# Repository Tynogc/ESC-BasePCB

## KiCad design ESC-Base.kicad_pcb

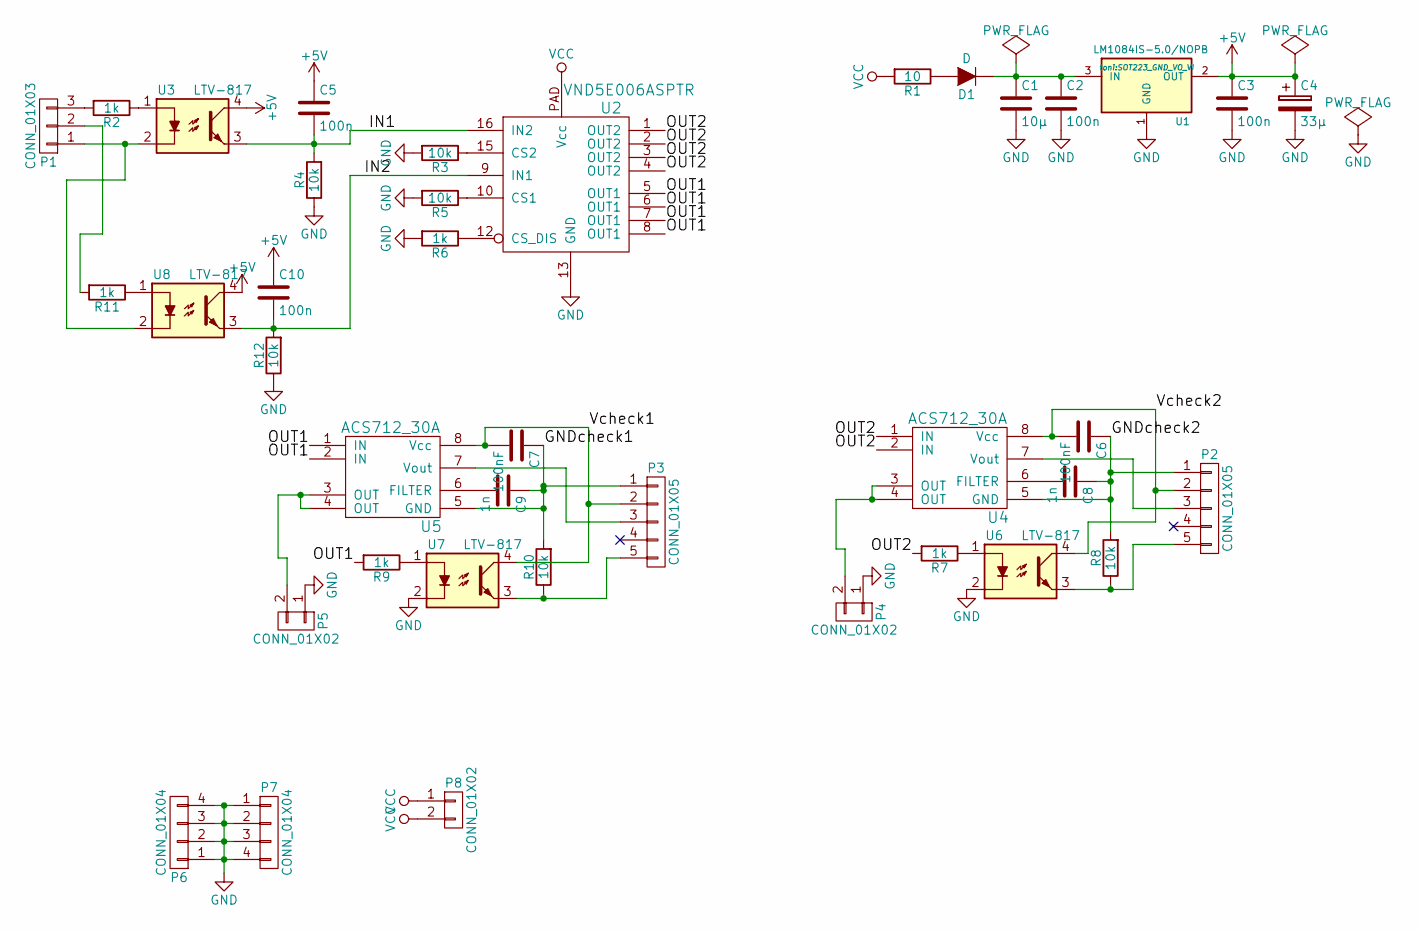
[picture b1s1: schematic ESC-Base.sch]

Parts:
C1: 10µ; C_0805_HandSoldering
C2, C3, C5, C10: 100n; C_0805_HandSoldering
C4: 33µ; c_elec_5x5.8
C6, C7: 100nF; C_0805_HandSoldering
C8, C9: 1n; C_0805_HandSoldering
D1: D; SOD-123
P1: CONN_01X03; Socket_Strip_Straight_1x03
P2, P3: CONN_01X05; Socket_Strip_Straight_1x05
P4, P5: CONN_01X02; PowerPole_1x2
P6, P7: CONN_01X04; Pin_Header_BIG_1x04
P8: CONN_01X02; Socket_Strip_Straight_1x02
R1: 10; R_0603_HandSoldering
R2, R6, R7, R9, R11: 1k; R_0603_HandSoldering
R3, R4, R5, R8, R10, R12: 10k; R_0603_HandSoldering
U1: LM1084IS-5.0/NOPB; SOT223_GND_VO_VI
U2: VND5E006ASPTR; POWER_SO16
U3, U6, U7, U8: LTV-817; SO-4
U4, U5: ACS712_30A; SOIC-8-N

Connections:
+5V: C3.1, C4.1, C5.1, C10.1, U1.2 (OUT), U3.4, U8.4
/GNDcheck1: C7.1, C9.1, P3.1, R10.2, U5.5 (GND)
/GNDcheck2: C6.1, C8.1, P2.1, R8.2, U4.5 (GND)
/IN1: C5.2, R4.2, U2.16 (IN2), U3.3
/IN2: C10.2, R12.2, U2.9 (IN1), U8.3
/OUT1: R9.2, U2.5 (OUT1), U2.6 (OUT1), U2.7 (OUT1), U2.8 (OUT1), U5.1 (IN), U5.2 (IN)
/OUT2: R7.2, U2.1 (OUT2), U2.2 (OUT2), U2.3 (OUT2), U2.4 (OUT2), U4.1 (IN), U4.2 (IN)
/Vcheck1: C7.2, P3.2, U5.8 (Vcc), U7.4
/Vcheck2: C6.2, P2.2, U4.8 (Vcc), U6.4
GND: C1.2, C2.2, C3.2, C4.2, P4.1, P5.1, P6.1, P6.2, P6.3, P6.4, P7.1, P7.2, P7.3, P7.4, R3.2, R4.1, R5.2, R6.2, R12.1, U1.1 (GND), U2.13 (GND), U6.2, U7.2
unnamed: C1.1, C2.1, D1.1 (K), U1.3 (IN)
unnamed: C8.2, U4.6 (FILTER)
unnamed: C9.2, U5.6 (FILTER)
unnamed: D1.2 (A), R1.1
unnamed: P1.1, U3.2, U8.2
unnamed: P1.2, R11.2
unnamed: P1.3, R2.2
unnamed: P2.3, U4.7 (Vout)
unnamed: P2.5, R8.1, U6.3
unnamed: P3.3, U5.7 (Vout)
unnamed: P3.5, R10.1, U7.3
unnamed: P4.2, U4.3 (OUT), U4.4 (OUT)
unnamed: P5.2, U5.3 (OUT), U5.4 (OUT)
unnamed: R2.1, U3.1
unnamed: R3.1, U2.15 (CS2)
unnamed: R5.1, U2.10 (CS1)
unnamed: R6.1, U2.12 (CS_DIS)
unnamed: R7.1, U6.1
unnamed: R9.1, U7.1
unnamed: R11.1, U8.1
VCC: P8.1, P8.2, R1.2, U2.PAD (Vcc)

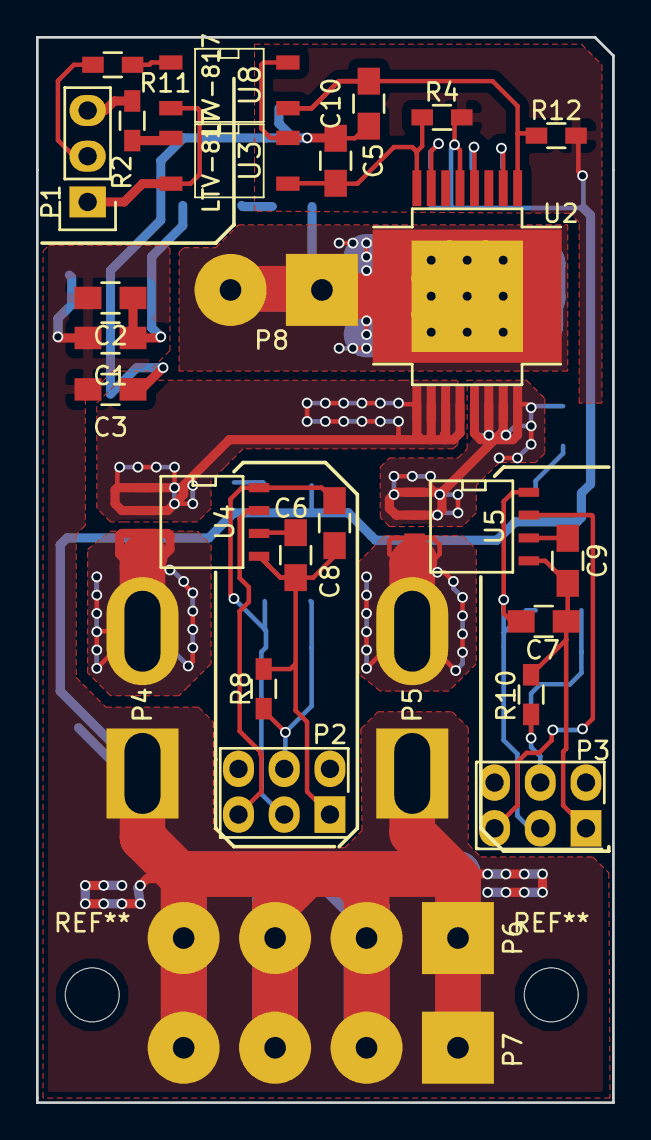
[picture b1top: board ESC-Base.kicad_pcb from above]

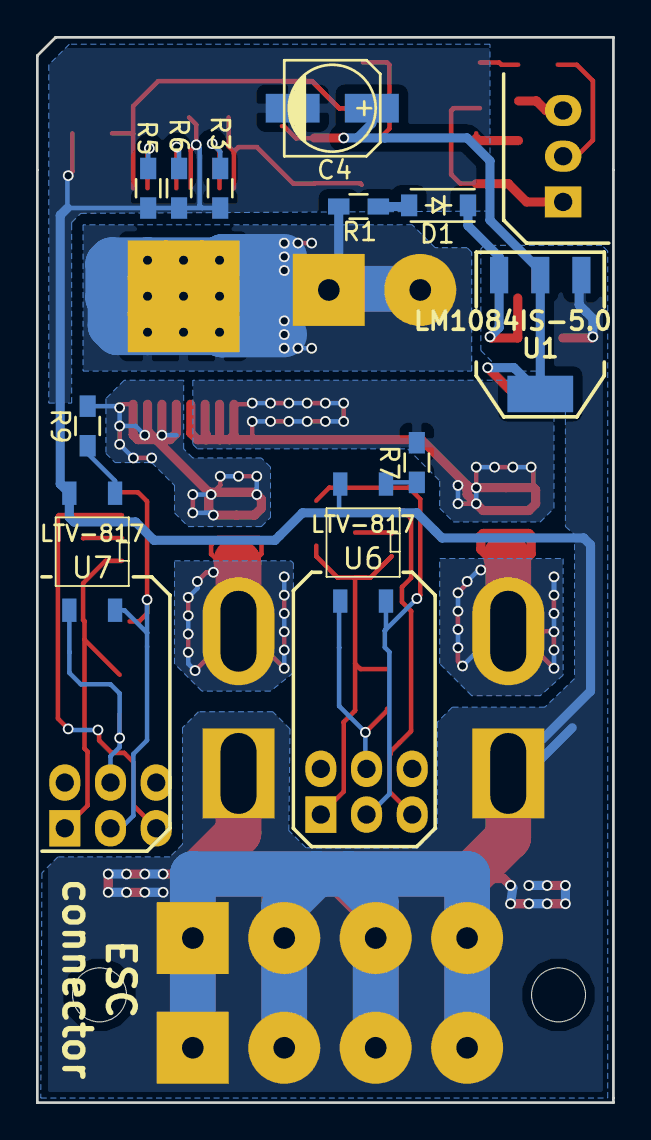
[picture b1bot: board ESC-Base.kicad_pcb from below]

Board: 2 copper layers, 32.0 x 59.2 mm, 39 parts (11 on the bottom side), 31 nets.

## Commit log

2015-11-23 Inital commit
2015-11-23 Layout begonnen
2015-11-23 Netzliste dazu
2015-11-24 Weiter gearbeitet...
2015-12-01 Kleinere Optimierung+Netlist-Fix
2015-12-04 Bohrungen, Lötstopplack und Bestückungsdruck: Alles Fertig!
2015-12-04 Gerber erstellt
